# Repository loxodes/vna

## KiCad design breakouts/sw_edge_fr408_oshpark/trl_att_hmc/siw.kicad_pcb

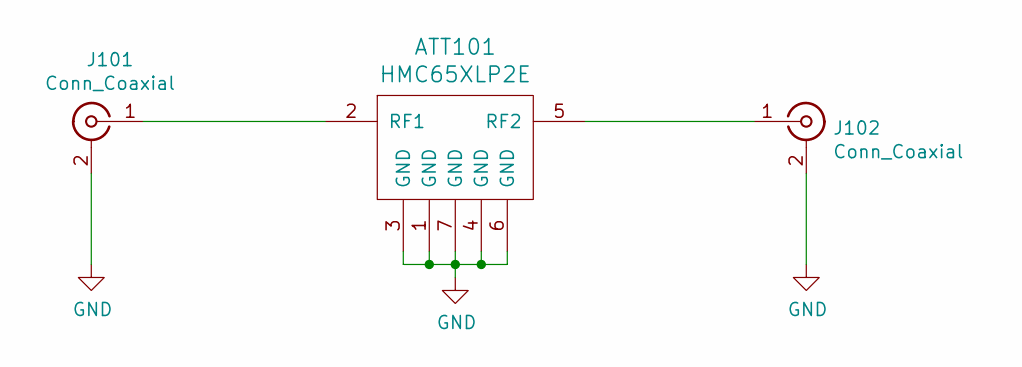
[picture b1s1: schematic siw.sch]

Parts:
ATT101: HMC65XLP2E; LP2E_DFN6_2x2mm_Pitch0.60mm
J101, J102: Conn_Coaxial; sw_edge_oshpark_4layer

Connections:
GND: ATT101.1 (GND), ATT101.3 (GND), ATT101.4 (GND), ATT101.6 (GND), ATT101.7 (GND), J101.2 (Ext), J102.2 (Ext)
unnamed: ATT101.2 (RF1), J101.1 (In)
unnamed: ATT101.5 (RF2), J102.1 (In)

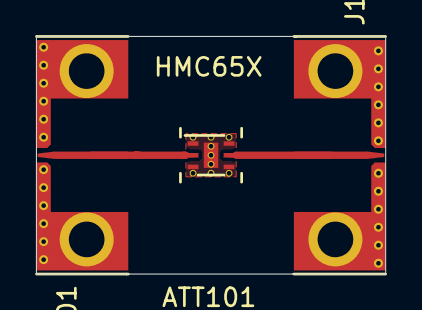
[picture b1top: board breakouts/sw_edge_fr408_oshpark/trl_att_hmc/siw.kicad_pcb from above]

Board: 4 copper layers, 19.4 x 13.2 mm, 3 parts (0 on the bottom side), 3 nets.

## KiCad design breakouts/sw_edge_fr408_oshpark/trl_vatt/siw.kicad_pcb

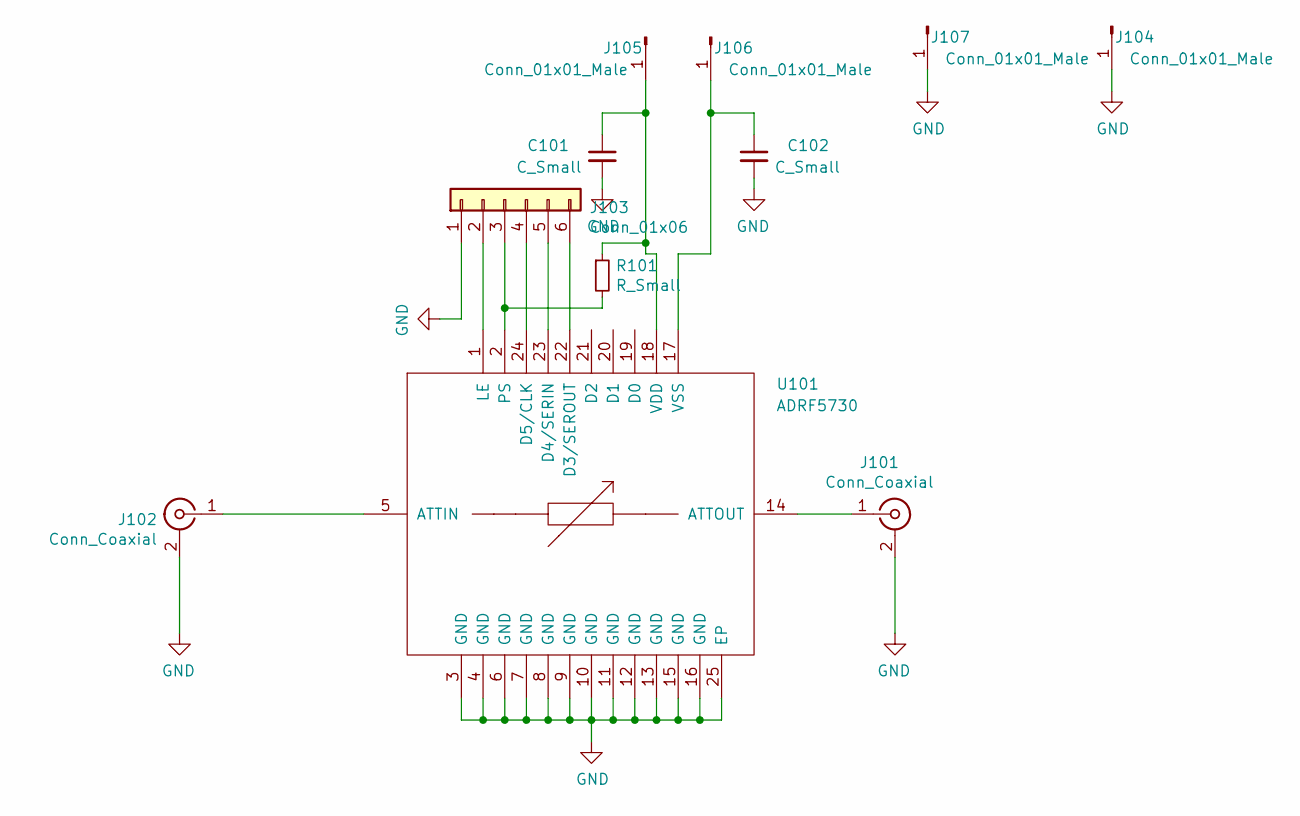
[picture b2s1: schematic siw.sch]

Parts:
C101, C102: C_Small; C_0402
J101, J102: Conn_Coaxial; sw_edge_oshpark_4layer
J103: Conn_01x06; Pin_Header_Straight_1x06
J104, J105, J106, J107: Conn_01x01_Male; TURRET_MILLMAX_2101
R101: R_Small; R_0402
U101: ADRF5730; QFN-24-1EP_4x4mm_Pitch0.5mm

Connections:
GND: C101.2, C102.2, J101.2 (Ext), J102.2 (Ext), J103.1, J104.1, J107.1, U101.3 (GND), U101.4 (GND), U101.6 (GND), U101.7 (GND), U101.8 (GND), U101.9 (GND), U101.10 (GND), U101.11 (GND), U101.12 (GND), U101.13 (GND), U101.15 (GND), U101.16 (GND), U101.25 (EP)
unnamed: C101.1, J105.1, R101.1, U101.18 (VDD)
unnamed: C102.1, J106.1, U101.17 (VSS)
unnamed: J101.1 (In), U101.14 (ATTOUT)
unnamed: J102.1 (In), U101.5 (ATTIN)
unnamed: J103.2, U101.1 (LE)
unnamed: J103.3, R101.2, U101.2 (PS)
unnamed: J103.4, U101.24 (D5/CLK)
unnamed: J103.5, U101.23 (D4/SERIN)
unnamed: J103.6, U101.22 (D3/SEROUT)

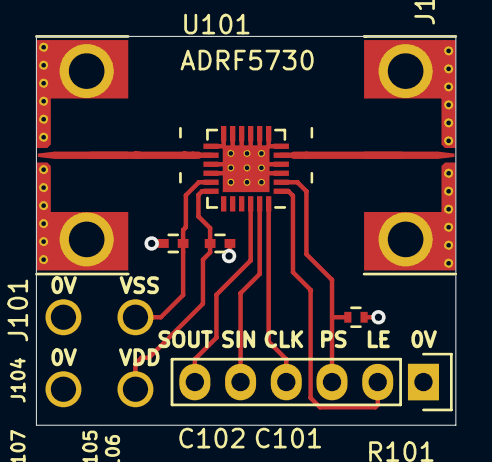
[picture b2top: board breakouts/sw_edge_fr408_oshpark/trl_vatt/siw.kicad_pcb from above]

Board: 4 copper layers, 23.3 x 21.6 mm, 11 parts (0 on the bottom side), 10 nets.

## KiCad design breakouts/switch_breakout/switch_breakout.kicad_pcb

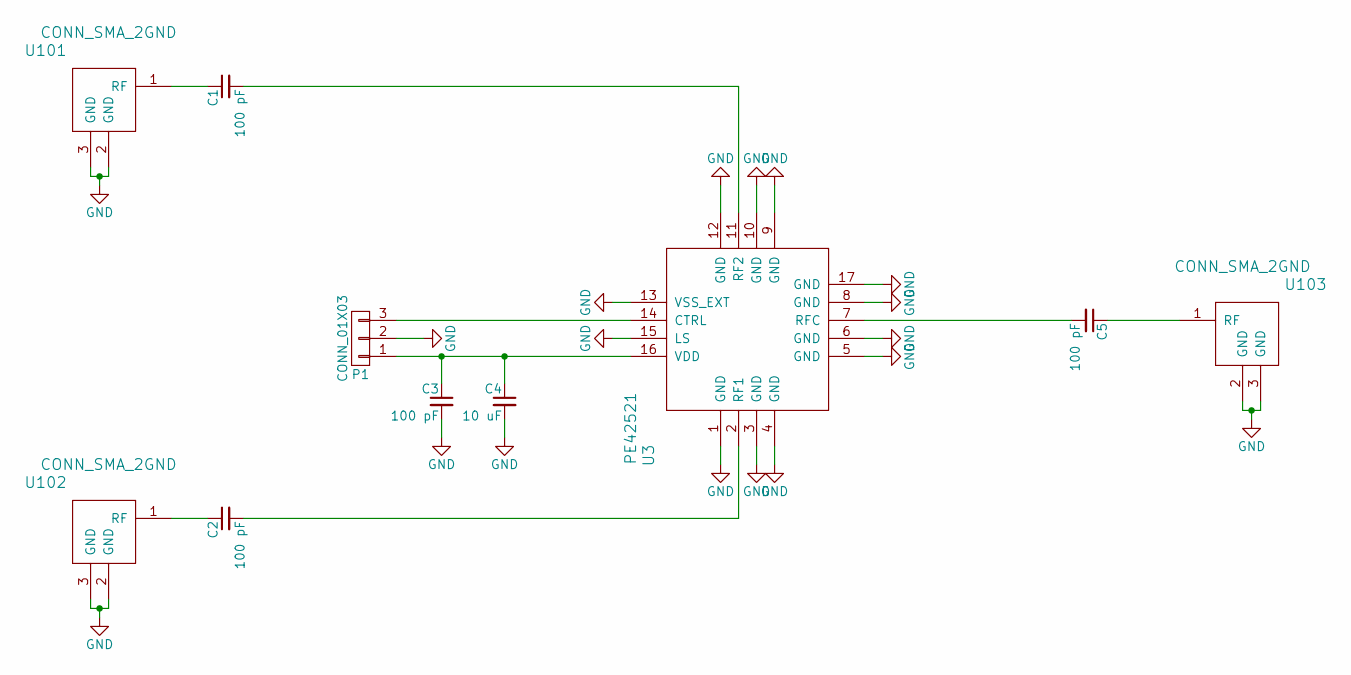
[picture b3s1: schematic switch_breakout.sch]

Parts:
C1, C2, C3, C5: 100 pF; C_0402
C4: 10 uF; C_0805
P1: CONN_01X03; Pin_Header_Straight_1x03
U3: PE42521; QFN-16-1EP_3x3mm_Pitch0.5mm
U101, U102, U103: CONN_SMA_2GND; SMA_CPW_1MM_.2MM

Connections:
GND: C3.2, C4.2, P1.2, U3.1 (GND), U3.3 (GND), U3.4 (GND), U3.5 (GND), U3.6 (GND), U3.8 (GND), U3.9 (GND), U3.10 (GND), U3.12 (GND), U3.13 (VSS_EXT), U3.15 (LS), U3.17 (GND), U101.2 (GND), U101.3 (GND), U102.2 (GND), U102.3 (GND), U103.2 (GND), U103.3 (GND)
unnamed: C1.1, U101.1 (RF)
unnamed: C1.2, U3.11 (RF2)
unnamed: C2.1, U102.1 (RF)
unnamed: C2.2, U3.2 (RF1)
unnamed: C3.1, C4.1, P1.1, U3.16 (VDD)
unnamed: C5.1, U103.1 (RF)
unnamed: C5.2, U3.7 (RFC)
unnamed: P1.3, U3.14 (CTRL)

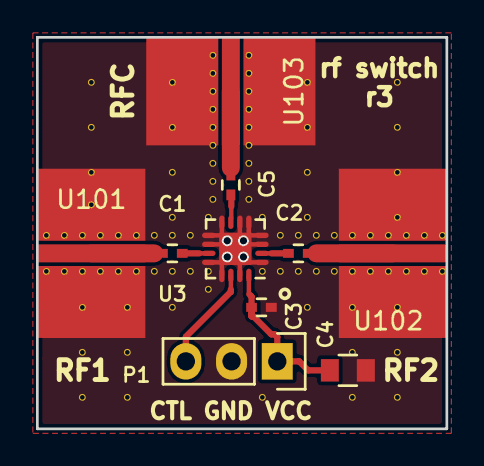
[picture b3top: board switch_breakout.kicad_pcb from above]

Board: 4 copper layers, 22.8 x 21.8 mm, 10 parts (0 on the bottom side), 9 nets.
